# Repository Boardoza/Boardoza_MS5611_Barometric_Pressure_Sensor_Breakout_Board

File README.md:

# Boardoza MS5611 Barometric Pressure Sensor Breakout Board

The **Boardoza MS5611** is a **high-precision barometric pressure sensor module** designed for **altitude measurement, weather monitoring, and industrial pressure sensing**. It integrates the **MS5611-01BA03** digital pressure sensor, providing accurate pressure readings with ultra-low power consumption.  

This module operates with **3.3V or 5V**, making it compatible with a wide range of microcontrollers. It communicates via **I<sup>2</sup>C by default**, but can be switched to **SPI mode** using the **PS pin**. The **CSB, SDO, and PS pins operate at 3.3V**, ensuring easy interfacing with low-power microcontrollers.  

## [Click here to purchase!](https://www.ozdisan.com/maker-ve-iot-urunleri/boardoza/boardoza-modulleri/BOARDOZA-MS5611/1202433)

|Front Side|Back Side|
|:---:|:---:|
| | |

---

## Key Features

- **High-Precision Barometric Pressure Sensor:** Ideal for altitude measurement, weather monitoring, and UAV applications.  
- **24-bit High-Resolution Output:** Ultra-precise pressure measurement using an integrated 24-bit ADC.  
- **Flexible Power Compatibility:** Operates with **3.3V or 5V**, making it suitable for various MCUs.  
- **I<sup>2</sup>C and SPI Support:** Default interface is **I<sup>2</sup>C**, but can be configured to **SPI mode** using the **PS pin**.  
- **Ultra-Low Power Consumption:** Optimized for battery-powered applications.  

---

## Technical Specifications

**Model:** MS5611-01BA03  
**Input Voltage:** 3.3V - 5.5V  
**Voltage Input Type:** 4-pin 2.50mm header  
**Interface:** I<sup>2</sup>C (default), SPI (configurable)  
**Functions:** High-Precision Barometric Pressure Measurement  
**ADC Resolution:** 24-bit  
**Operating Pressure Range:** 450 to 1100 mbar (Full Accuracy)  
**Extended Pressure Range:** 10 to 1200 mbar (Linear ADC Range)  
**Operating Temperature:** -40°C ~ +85°C  
**Board Dimensions:** 20mm x 20mm  

---

## Board Pinout

### **( J1 ) I<sup>2</sup>C Communication Pins**  

| Pin Number | Pin Name | Description |
|:---:|:---:|---|
| 1 | VCC | Power Supply (3.3V - 5.5V) |
| 2 | SCL | I<sup>2</sup>C Serial Clock Pin |
| 3 | SDA | I<sup>2</sup>C Serial Data Pin |
| 4 | GND | Ground |

### **( J2 ) SPI Mode & Configuration Pins**  

| Pin Number | Pin Name | Description |
|:---:|:---:|---|
| 1 | CSB | Chip select (active low), internally pulled down to ground with a pull-down resistor. |
| 2 | SDO | Serial data output. |
| 3 | PS | Protocol selection:<ul><li>PS High (3.3V) = I<sup>2</sup>C (Default address: 0x77)</li><li>PS Low (GND) = SPI Mode</li></ul> (Internally pulled up to 3.3V with a pull-up resistor). |

---

## Board Dimensions

---

## Step Files

[Boardoza MS5611.step](./assets/MS5611%20Step.step)

---

## Datasheet

[Boardoza MS5611 Datasheet.pdf](./assets/MS5611%20Datasheet.pdf)

---

## Version History

- V1.0.0 - Initial Release

---

## Support

- If you have any questions or need support, please contact <support@boardoza.com>

---

## License

Shield: [![CC BY-SA 4.0][cc-by-sa-shield]][cc-by-sa]

This work is licensed under a [Creative Commons Attribution-ShareAlike 4.0 International License][cc-by-sa].

[![CC BY-SA 4.0][cc-by-sa-image]][cc-by-sa]

[cc-by-sa]: http://creativecommons.org/licenses/by-sa/4.0/
[cc-by-sa-image]: https://licensebuttons.net/l/by-sa/4.0/88x31.png
[cc-by-sa-shield]: https://img.shields.io/badge/License-CC%20BY--SA%204.0-lightgrey.svg

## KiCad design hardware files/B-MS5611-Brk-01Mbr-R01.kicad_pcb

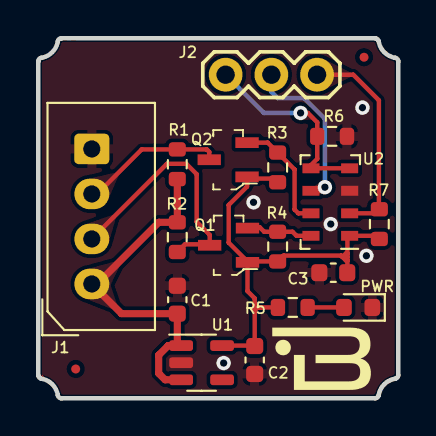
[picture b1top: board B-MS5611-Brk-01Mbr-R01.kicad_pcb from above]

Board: 2 copper layers, 20.0 x 20.0 mm, 17 parts (0 on the bottom side), 11 nets.

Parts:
C1, C2: 1uF; C_0603_1608Metric
C3: 100nF; C_0603_1608Metric
J1: MOLEX_CONNECTOR_1X4; 2317-04S_1x04_P2.50mm_Vertical
J2: CONN_03; 1X03
PWR: LED POWER; LED_0603_1608Metric
Q1, Q2: 2N7002_R1_00001; SOT-23-3
R1, R2, R3, R4, R5, R6, R7: 10K; R_0603_1608Metric
U1: TLV73333PDBVR; SOT-23-5
U2: MS5611-01BA; LGA-8_3x5mm_P1.25mm

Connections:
+3V3: C2.1, C3.1, Q1.1 (G), Q2.1 (G), R3.1, R4.1, R5.1, R7.2, U1.5 (OUT), U2.1 (VDD)
CSB: J2.3, R6.1, U2.4 (CSB), U2.5 (CSB)
GND: C1.2, C2.2, C3.2, J1.4, PWR.1 (K), R6.2, U1.2 (GND), U2.3 (GND)
unnamed: PWR.2 (A), R5.2
PS: J2.1, R7.1, U2.2 (PS)
SCL: J1.2, Q1.3 (D), R2.2
SCL_3.3: Q1.2 (S), R4.2, U2.8 (SCLK)
SDA: J1.3, Q2.3 (D), R1.2
SDA_3.3: Q2.2 (S), R3.2, U2.7 (SDI/SDA)
SDO: J2.2, U2.6 (SDO)
VCC: C1.1, J1.1, R1.1, R2.1, U1.1 (IN), U1.3 (EN)
